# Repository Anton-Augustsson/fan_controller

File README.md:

# fan-controller

## Arduino 
the code is in arduino folder, library is not inluded.

## Kicad
is in kicad, BOM is not included, library is not inluded.

## Seed
is the PCB pruduser. Allfiles is abluge to be sent inorder to get valid cad drwing.

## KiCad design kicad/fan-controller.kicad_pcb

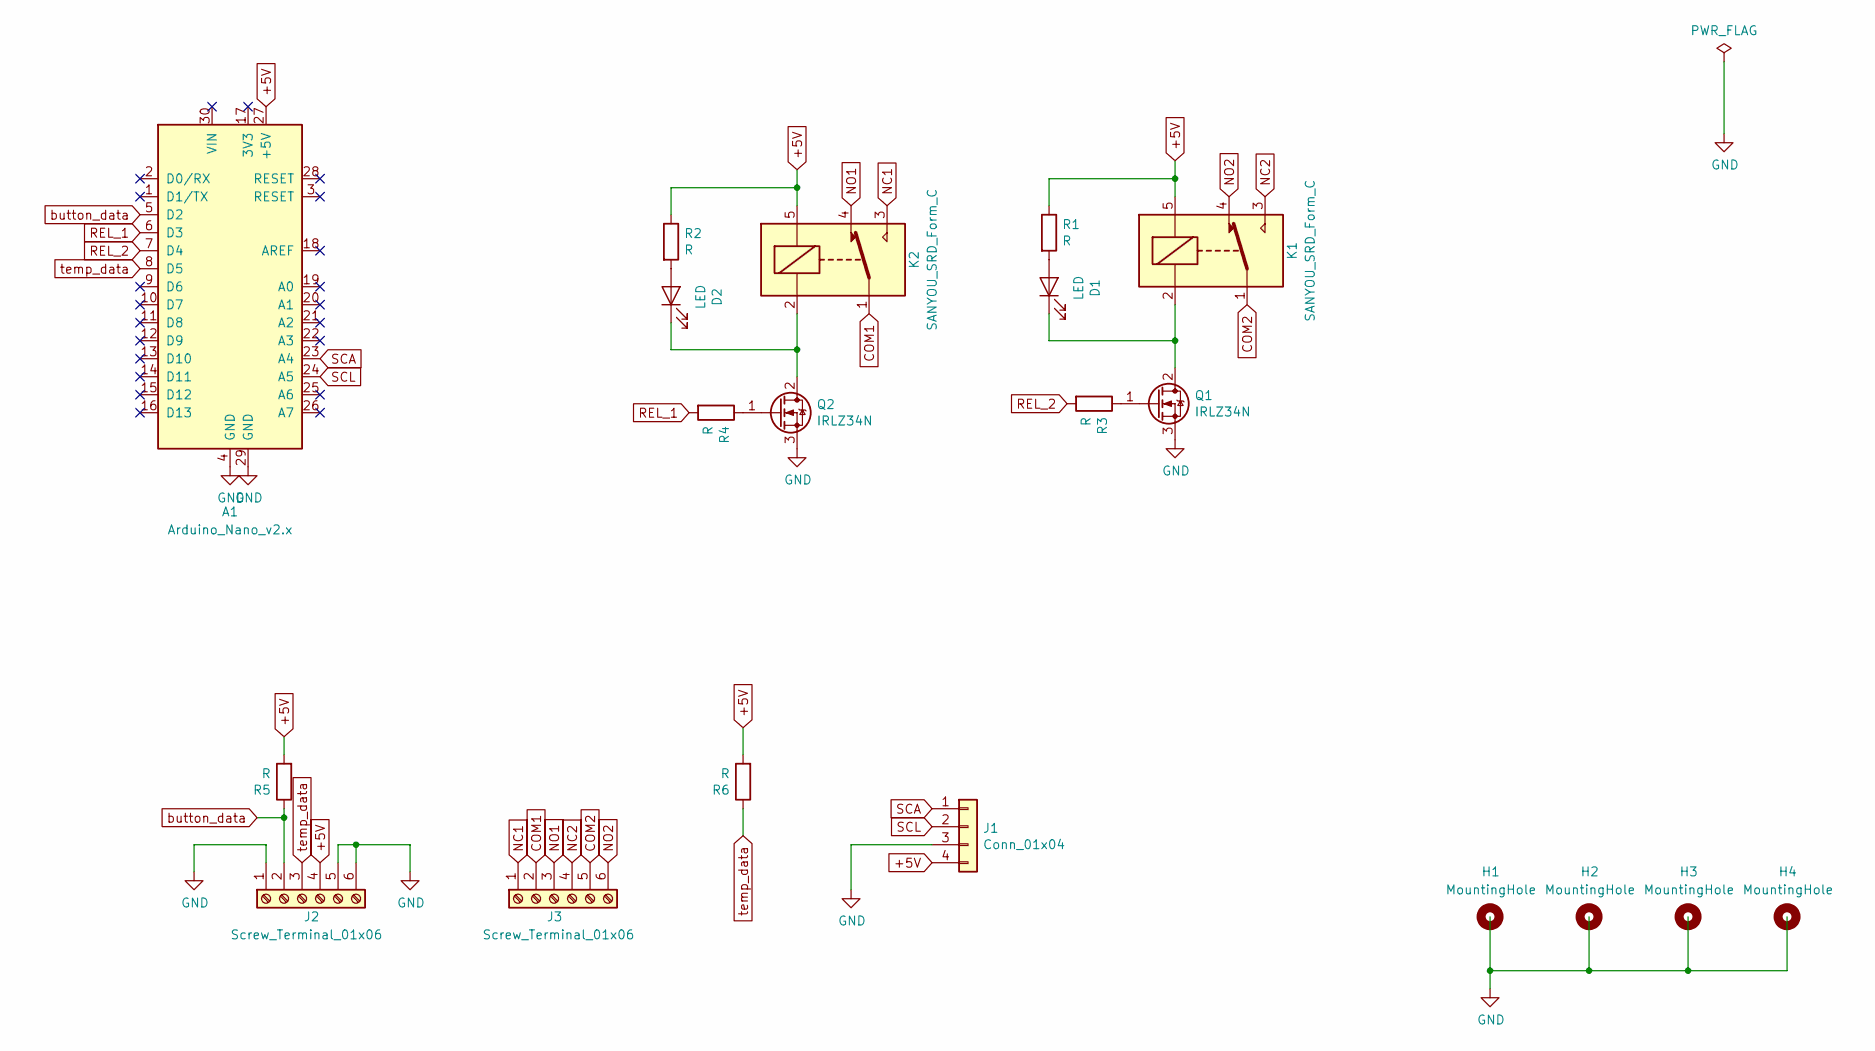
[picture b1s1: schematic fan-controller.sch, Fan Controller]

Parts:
A1: Arduino_Nano_v2.x; Arduino_Nano
D1, D2: LED; LED_D3.0mm
H1, H2, H3, H4: MountingHole; MountingHole_3.2mm_M3
J1: Conn_01x04; PinHeader_1x04_P2.54mm_Vertical
J2, J3: Screw_Terminal_01x06; TerminalBlock_Phoenix_MKDS-1,5-6-5.08_1x06_P5.08mm_Horizont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
K1, K2: SANYOU_SRD_Form_C; Relay_SPDT_Omron-G5LE-1
Q1, Q2: IRLZ34N; TO-220-3_Vertical
R1, R2, R3, R4, R5, R6: R; R_Axial_DIN0207_L6.3mm_D2.5mm_P10.16mm_Horizontal

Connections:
+5V: A1.27 (+5V), J1.4, J2.4, K1.5, K2.5, R1.1, R2.1, R5.2, R6.2
COM1: J3.2, K2.1
COM2: J3.5, K1.1
GND: A1.4 (GND), A1.29 (GND), J1.3, J2.1, J2.5, J2.6, Q1.3 (S), Q2.3 (S)
NC1: J3.1, K2.3
NC2: J3.4, K1.3
NO1: J3.3, K2.4
NO2: J3.6, K1.4
unnamed: D1.1 (K), K1.2, Q1.2 (D)
unnamed: D1.2 (A), R1.2
unnamed: D2.1 (K), K2.2, Q2.2 (D)
unnamed: D2.2 (A), R2.2
unnamed: Q1.1 (G), R3.1
unnamed: Q2.1 (G), R4.1
REL_1: A1.6 (D3), R4.2
REL_2: A1.7 (D4), R3.2
SCA: A1.23 (A4), J1.1
SCL: A1.24 (A5), J1.2
button_data: A1.5 (D2), J2.2, R5.1
temp_data: A1.8 (D5), J2.3, R6.1

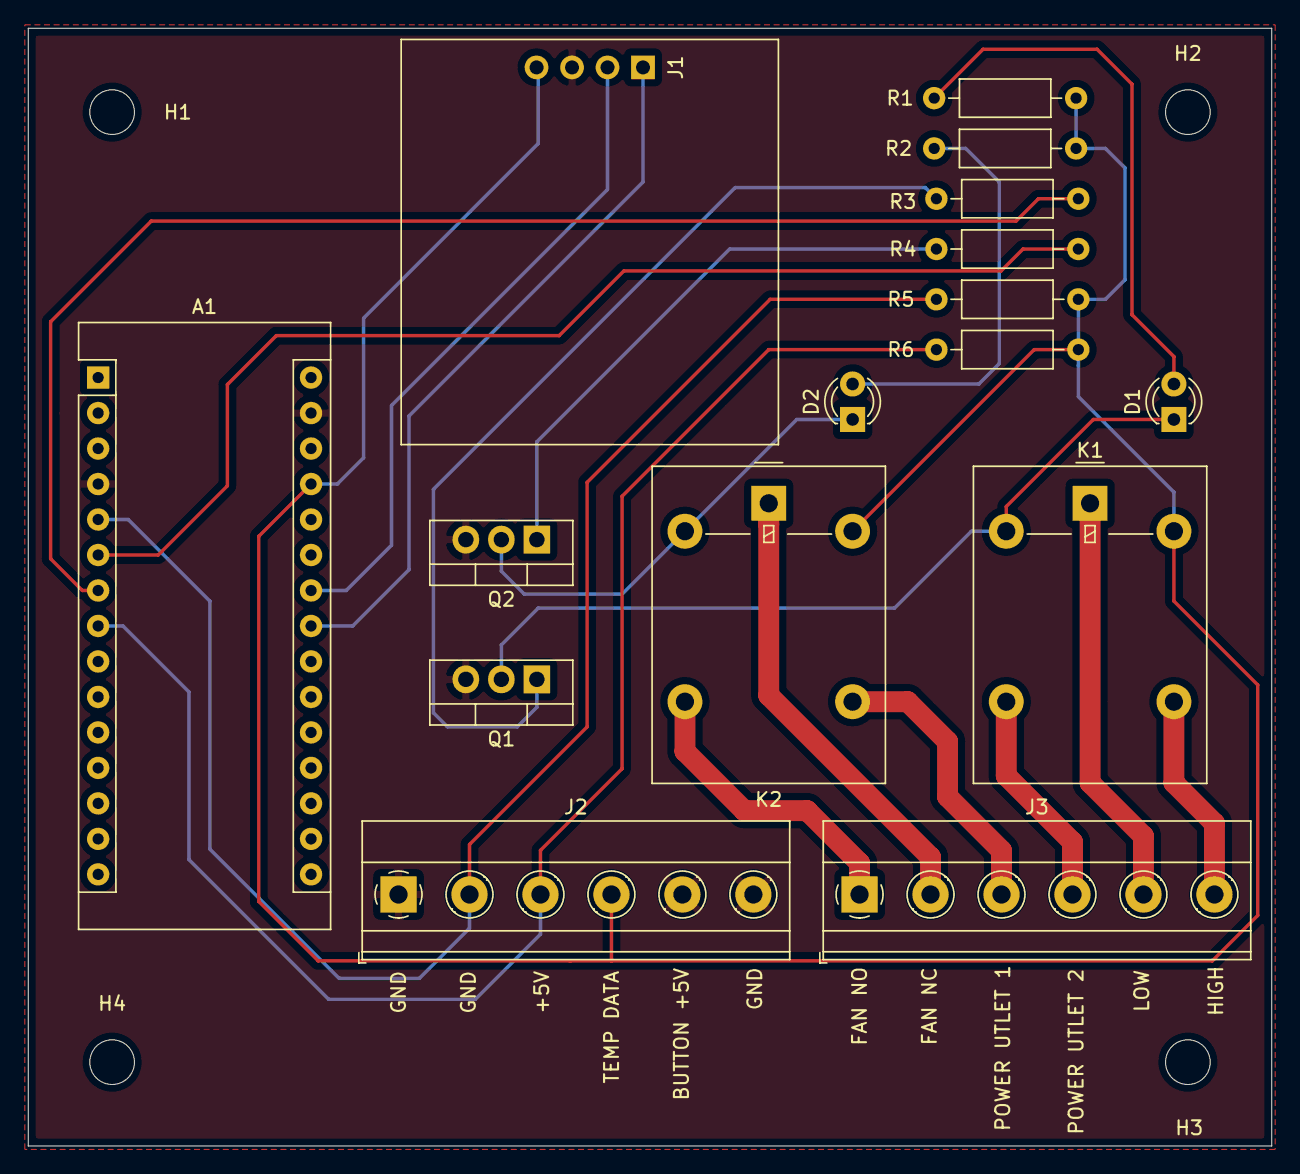
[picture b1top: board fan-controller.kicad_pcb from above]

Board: 2 copper layers, 89.0 x 80.0 mm, 20 parts (0 on the bottom side), 20 nets.

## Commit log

2019-05-10 inital commit
2019-05-10 updated temp liment
2020-02-18 Readme update
